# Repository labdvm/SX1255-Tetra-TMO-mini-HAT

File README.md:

# SX1255-Tetra-TMO-mini-HAT

same as SX1255 Tetra-TMO HS HAT but without PA.
# This version of mini HAT is with LowPass filter on the TX and BandPass filter on the RX.
# RPi4/5 or RPi Zero 2W, fast-write micro-sd card.
# The eeprom is for HW-ID and if cannot be programmed by the procedures then you must programm with eeprom programmator. " https://github.com/tejeez/sxxcvr/blob/main/dts/README.md ".
# For Tetra-TMO Base Station this is the installing procedures, " https://github.com/MidnightBlueLabs/tetra-bluestation-docs/wiki ".
# BlueStation, https://github.com/MidnightBlueLabs/tetra-bluestation
# FlowStation, https://github.com/razvanzeces/flowstation
# BlueStation Tetra TMO configurator " https://bluestation.russel053.com/ "

Install FlowStation ---for sxceiver---
# 1. Install Trixie 64bit-LITE
# 2. 
# sudo apt update
# sudo apt install git make g++ cmake
# sudo apt install libsoapysdr-dev
# sudo apt install soapysdr-tools
# sudo apt install libasound2-dev
# sudo apt install clang llvm-dev libclang-dev

3. Rust
# curl https://sh.rustup.rs -sSf | sh

4. SoapySX "enable SPI and I2C on the RPi"
# cd
# git clone "https://github.com/tejeez/sxxcvr.git"
# cd sxxcvr/SoapySX
# mkdir build
# cd build
# cmake ..
# make
# sudo make install
# sudo ldconfig

Check that the driver is available:
# SoapySDRUtil --info

Check that the device is detected:
# ls -l /proc/device-tree/hat
# SoapySDRUtil --probe=driver=sx

5. The FlowStation
# git clone https://github.com/razvanzeces/flowstation
# cd flowstation
# . "$HOME/.cargo/env"
# cargo build --release
# cp example_config/config.toml config.toml
# nano config.toml (configure the base station)

6. Run
# ./target/release/bluestation-bs ./config.toml

7. Update
# git pull
# cargo build --release

# Z32IT

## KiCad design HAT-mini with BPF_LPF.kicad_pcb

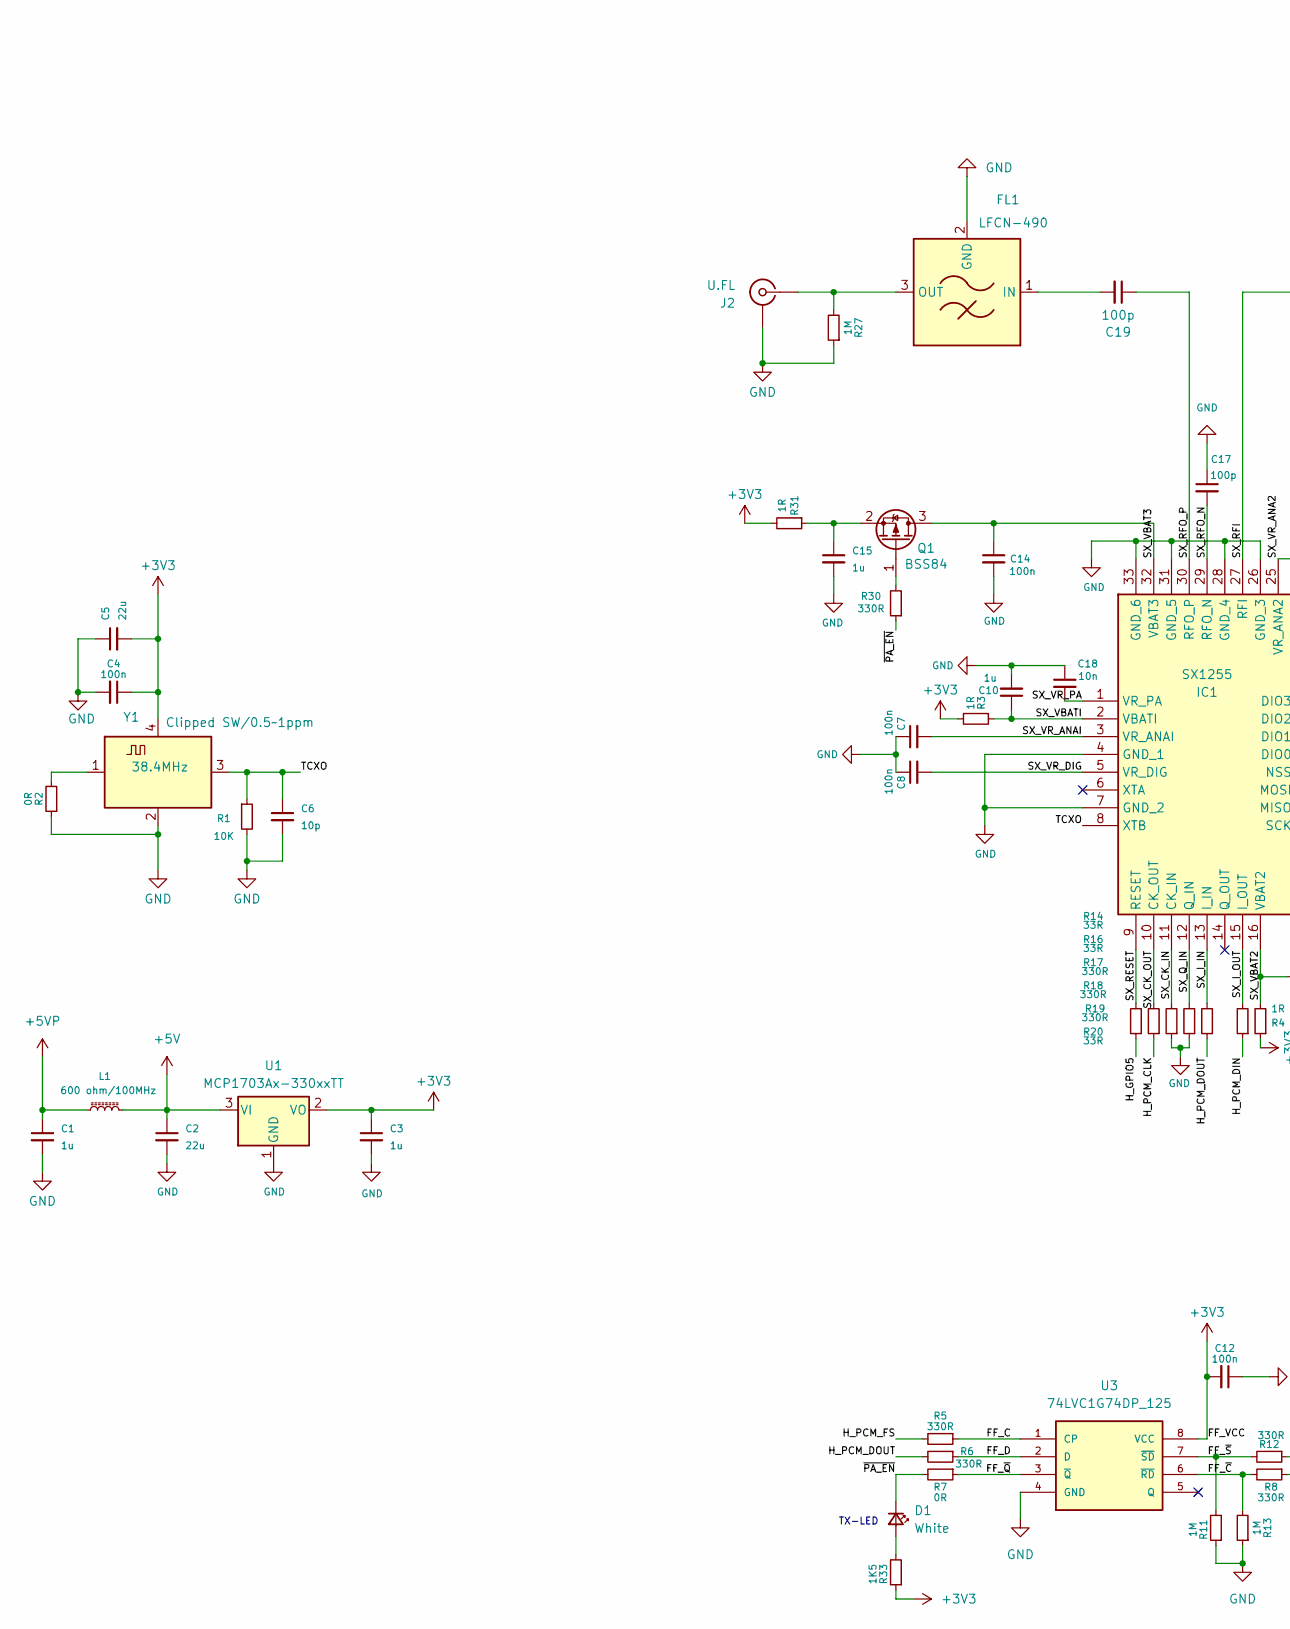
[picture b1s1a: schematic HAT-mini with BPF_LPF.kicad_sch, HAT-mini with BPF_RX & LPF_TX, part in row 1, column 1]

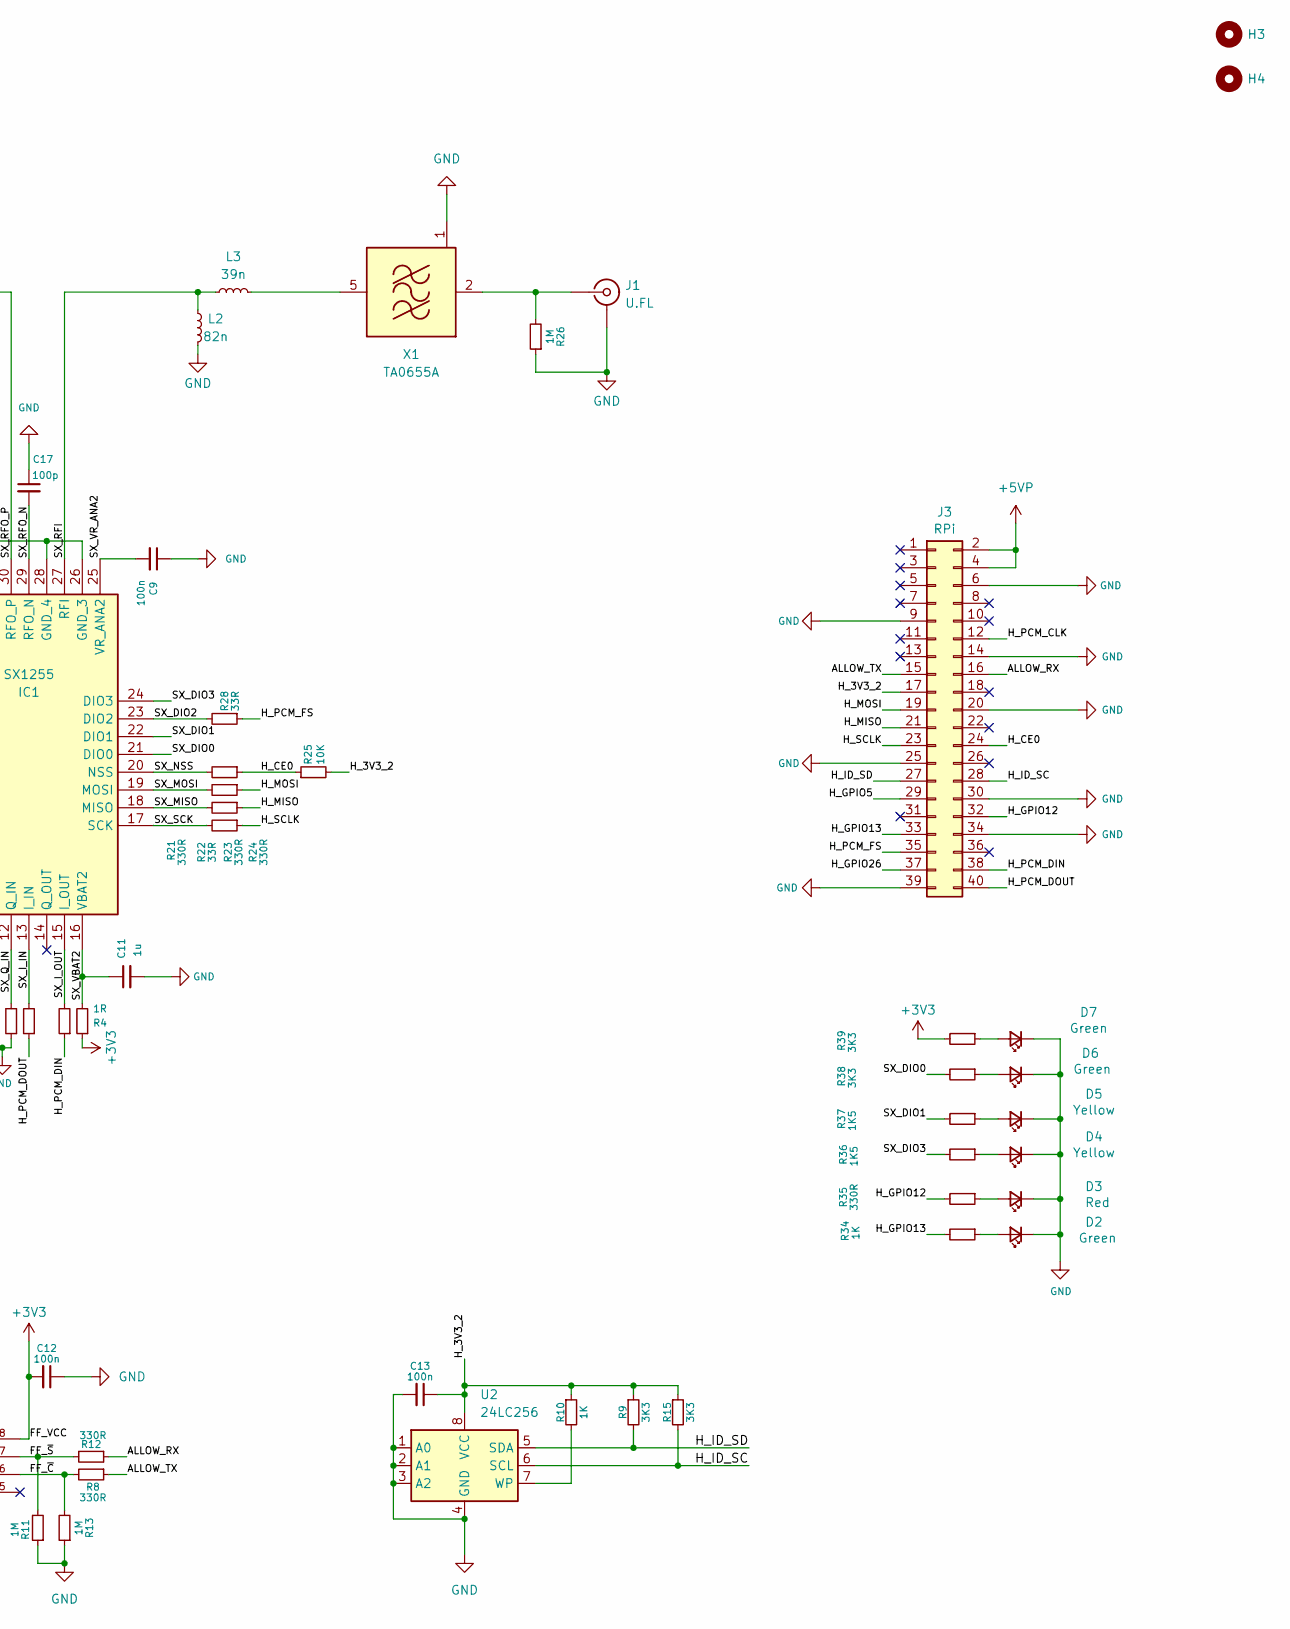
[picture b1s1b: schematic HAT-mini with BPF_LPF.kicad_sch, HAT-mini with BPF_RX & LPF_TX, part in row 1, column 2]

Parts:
C1, C3, C10, C11, C15: 1u; C_0603_1608Metric; Part Number 311-3484-1-ND
C2, C5: 22u; C_1206_3216Metric; Part Number 1276-3148-1-ND
C4: 100n; C_0603_1608Metric; Part Number 720-1688-1-ND
C6: 10p; C_0603_1608Metric; Part Number 399-14932-1-ND
C7, C8: 100n; C_0402_1005Metric_Pad0.74x0.62mm_HandSolder; Part Number 720-1688-1-ND
C9, C12, C13, C14: 100n; C_0402_1005Metric_Pad0.74x0.62mm_HandSolder
C17, C19: 100p; C_0402_1005Metric_Pad0.74x0.62mm_HandSolder
C18: 10n; C_0402_1005Metric_Pad0.74x0.62mm_HandSolder; Part Number 399-C0603C103K8RACTUCT-ND
D1: White; LED_0603_1608Metric_Pad1.05x0.95mm_HandSolder; Part Number 160-LTST-T180UWETCT-ND
D2, D6, D7: Green; LED_0603_1608Metric_Pad1.05x0.95mm_HandSolder; Part Number 754-APT1608SGD3CT-ND
D3: Red; LED_0603_1608Metric_Pad1.05x0.95mm_HandSolder; Part Number 160-1479-1-ND
D4, D5: Yellow; LED_0603_1608Metric_Pad1.05x0.95mm_HandSolder; Part Number 160-1437-1-ND
FL1: LFCN-490; Filter_Mini-Circuits_FV1206; Part Number 3157-LFCN-490+CT-ND
H3, H4: MountingHole; MountingHole_2.7mm_M2.5_DIN965
IC1: SX1255; QFN-32-1EP_5x5mm_P0.5mm_EP3.3x3.3mm_ThermalVias; Part Number SX1255IWLTRTCT-ND
J1, J2: U.FL; Part Number 343-CONMHF1-SMD-G-TCT-ND
J3: RPi; PinSocket_2x20_P2.54mm_Vertical
L1: 600 ohm/100MHz; L_0603_1608Metric; Part Number 490-1046-1-ND
L2: 82n; L_0603_1608Metric; Part Number 712-LRC0603CJ82NGV001TCT-ND
L3: 39n; L_0603_1608Metric; Part Number 712-LRC0603CJ39NGV001TCT-ND
Q1: BSS84; SOT-23; Part Number 3372-BSS84TR-ND
R1: 10K; R_0603_1608Metric; Part Number 541-10.0KHCT-ND
R2, R7: 0R; R_0402_1005Metric_Pad0.72x0.64mm_HandSolder
R3: 1R; R_0402_1005Metric_Pad0.72x0.64mm_HandSolder; Part Number 541-1.00HHCT-ND
R4, R31: 1R; R_0402_1005Metric_Pad0.72x0.64mm_HandSolder
R5, R6, R8, R12, R17, R18, R19, R21, R23, R24, R30, R35: 330R; R_0402_1005Metric_Pad0.72x0.64mm_HandSolder
R9, R15, R38, R39: 3K3; R_0402_1005Metric_Pad0.72x0.64mm_HandSolder
R10, R34: 1K; R_0402_1005Metric_Pad0.72x0.64mm_HandSolder
R11, R13, R26, R27: 1M; R_0402_1005Metric_Pad0.72x0.64mm_HandSolder
R14, R16, R20, R22, R28: 33R; R_0402_1005Metric_Pad0.72x0.64mm_HandSolder
R25: 10K; R_0402_1005Metric_Pad0.72x0.64mm_HandSolder
R33, R36, R37: 1K5; R_0402_1005Metric_Pad0.72x0.64mm_HandSolder
U1: MCP1703Ax-330xxTT; SOT-23
U2: 24LC256; SOIC-8_3.9x4.9mm_P1.27mm; Part Number 24LC256-I/SN-ND
U3: 74LVC1G74DP_125; SOP65P400X110-8N; Part Number 1727-5983-1-ND
X1: TA0655A; Filter_SAW-6_3.8x3.8mm
Y1: 38.4MHz; Crystal_SMD_3225-4Pin_3.2x2.5mm; Part Number 114-TG2520SMN38.4000M-MCGNNM3CT-ND

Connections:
+3V3: C3.1, C4.1, C5.2, C12.2, R3.2, R4.1, R31.2, R33.1, R39.2, U1.2 (VO), U3.8 (VCC), Y1.4 (VDD)
+5V: C2.1, L1.2, U1.3 (VI)
+5VP: C1.1, J3.2, J3.4, L1.1
/ALLOW_RX: J3.16, R12.1
/ALLOW_TX: J3.15, R8.1
/FF_C: R5.1, U3.1 (CP)
/FF_D: R6.1, U3.2 (D)
/FF_~C: R8.2, R13.2, U3.6 (~RD)
/FF_~Q: R7.1, U3.3 (~Q)
/FF_~S: R11.2, R12.2, U3.7 (~SD)
/H_3V3_2: C13.1, J3.17, R9.1, R10.1, R15.1, R25.2, U2.8 (VCC)
/H_CE0: J3.24, R24.1, R25.1
/H_GPIO5: J3.29, R14.1
/H_GPIO12: J3.32, R35.2
/H_GPIO13: J3.33, R34.2
/H_GPIO26: J3.37
/H_ID_SC: J3.28, R15.2, U2.6 (SCL)
/H_ID_SD: J3.27, R9.2, U2.5 (SDA)
/H_MISO: J3.21, R22.1
/H_MOSI: J3.19, R23.1
/H_PCM_CLK: J3.12, R16.1
/H_PCM_DIN: J3.38, R20.1
/H_PCM_DOUT: J3.40, R6.2, R19.1
/H_PCM_FS: J3.35, R5.2, R28.1
/H_SCLK: J3.23, R21.1
/SX_CK_IN: IC1.11 (CK_IN), R17.2
/SX_CK_OUT: IC1.10 (CK_OUT), R16.2
/SX_DIO0: IC1.21 (DIO0), R38.2
/SX_DIO1: IC1.22 (DIO1), R37.2
/SX_DIO2: IC1.23 (DIO2), R28.2
/SX_DIO3: IC1.24 (DIO3), R36.2
/SX_I_IN: IC1.13 (I_IN), R19.2
/SX_I_OUT: IC1.15 (I_OUT), R20.2
/SX_MISO: IC1.18 (MISO), R22.2
/SX_MOSI: IC1.19 (MOSI), R23.2
/SX_NSS: IC1.20 (NSS), R24.2
/SX_Q_IN: IC1.12 (Q_IN), R18.2
/SX_RESET: IC1.9 (RESET), R14.2
/SX_RFI: IC1.27 (RFI), L2.2, L3.2
/SX_RFO_N: C17.2, IC1.29 (RFO_N)
/SX_RFO_P: C19.1, IC1.30 (RFO_P)
/SX_SCK: IC1.17 (SCK), R21.2
/SX_VBAT2: C11.1, IC1.16 (VBAT2), R4.2
/SX_VBAT3: C14.1, IC1.32 (VBAT3), Q1.3 (D)
/SX_VBATI: C10.1, IC1.2 (VBATI), R3.1
/SX_VR_ANA2: C9.2, IC1.25 (VR_ANA2)
/SX_VR_ANAI: C7.2, IC1.3 (VR_ANAI)
/SX_VR_DIG: C8.2, IC1.5 (VR_DIG)
/SX_VR_PA: C18.2, IC1.1 (VR_PA)
/TCXO: C6.1, IC1.8 (XTB), R1.1, Y1.3 (OUT)
/~PA_EN: D1.1 (K), R7.2, R30.1
GND: C1.2, C2.2, C3.2, C4.2, C5.1, C6.2, C7.1, C8.1, C9.1, C10.2, C11.2, C12.1, C13.2, C14.2, C15.2, C17.1, C18.1, D2.1 (K), D3.1 (K), D4.1 (K), D5.1 (K), D6.1 (K), D7.1 (K), FL1.2 (GND), FL1.4 (GND), IC1.4 (GND_1), IC1.7 (GND_2), IC1.26 (GND_3), IC1.28 (GND_4), IC1.31 (GND_5), IC1.33 (GND_6), J1.2 (Ext), J2.2 (Ext), J3.6, J3.9, J3.14, J3.20, J3.25, J3.30, J3.34, J3.39, L2.1, R1.2, R2.1, R11.1, R13.1, R17.1, R18.1, R26.1, R27.1, U1.1 (GND), U2.1 (A0), U2.2 (A1), U2.3 (A2), U2.4 (GND), U3.4 (GND), X1.1 (GND), X1.3 (GND), X1.4 (GND), X1.6 (GND), Y1.2 (GND)
unnamed: D1.2 (A), R33.2
unnamed: D2.2 (A), R34.1
unnamed: D3.2 (A), R35.1
unnamed: D4.2 (A), R36.1
unnamed: D5.2 (A), R37.1
unnamed: D6.2 (A), R38.1
unnamed: D7.2 (A), R39.1
unnamed: C19.2, FL1.1 (IN)
unnamed: FL1.3 (OUT), J2.1 (In), R27.2
unnamed: J1.1 (In), R26.2, X1.2 (IN)
unnamed: Q1.1 (G), R30.2
unnamed: C15.1, Q1.2 (S), R31.1
unnamed: R10.2, U2.7 (WP)
unnamed: L3.1, X1.5 (OUT)
unnamed: R2.2, Y1.1 (Tri-State)

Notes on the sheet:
TX-LED

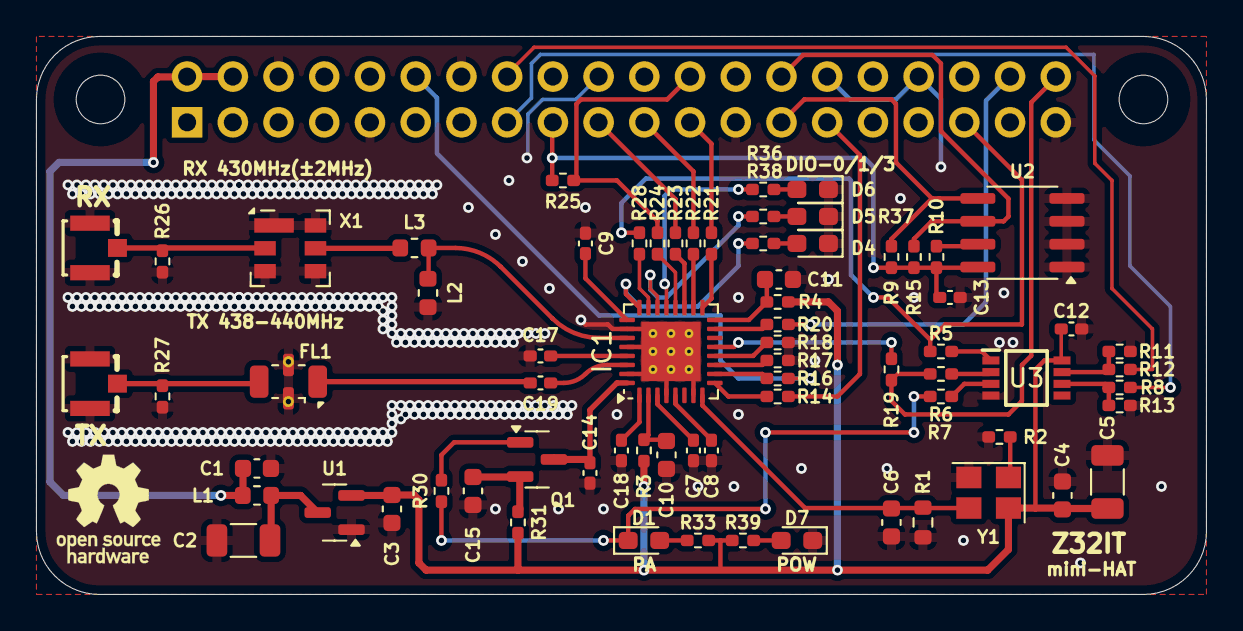
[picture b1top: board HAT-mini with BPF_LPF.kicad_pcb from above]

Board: 2 copper layers, 65.0 x 31.0 mm, 74 parts (1 on the bottom side), 62 nets.

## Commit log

2026-03-19 Update README with additional details and links
    Added additional information about the SX1255-Tetra-TMO-mini-HAT, including installation procedures and links to resources.
2026-03-19 Correct capitalization in README for BandPass filter
2026-03-19 Update eeprom programming instructions in README
    Clarified eeprom programming instructions and added link for eeprom.bin generation.
2026-03-20 Revise README for RPi compatibility and storage options
    Updated compatibility and hardware requirements for mini HAT.
2026-03-30 Add donation link to README
    Added donation link for support.
2026-04-10 Update BlueStation Tetra TMO configurator URL
2026-05-04 Update README to clarify project details
    Removed mention of modified SXceiver and added donation link.
2026-05-12 Revise README with EEPROM and FlowStation details
    Updated instructions for EEPROM programming and added installation steps for FlowStation.
